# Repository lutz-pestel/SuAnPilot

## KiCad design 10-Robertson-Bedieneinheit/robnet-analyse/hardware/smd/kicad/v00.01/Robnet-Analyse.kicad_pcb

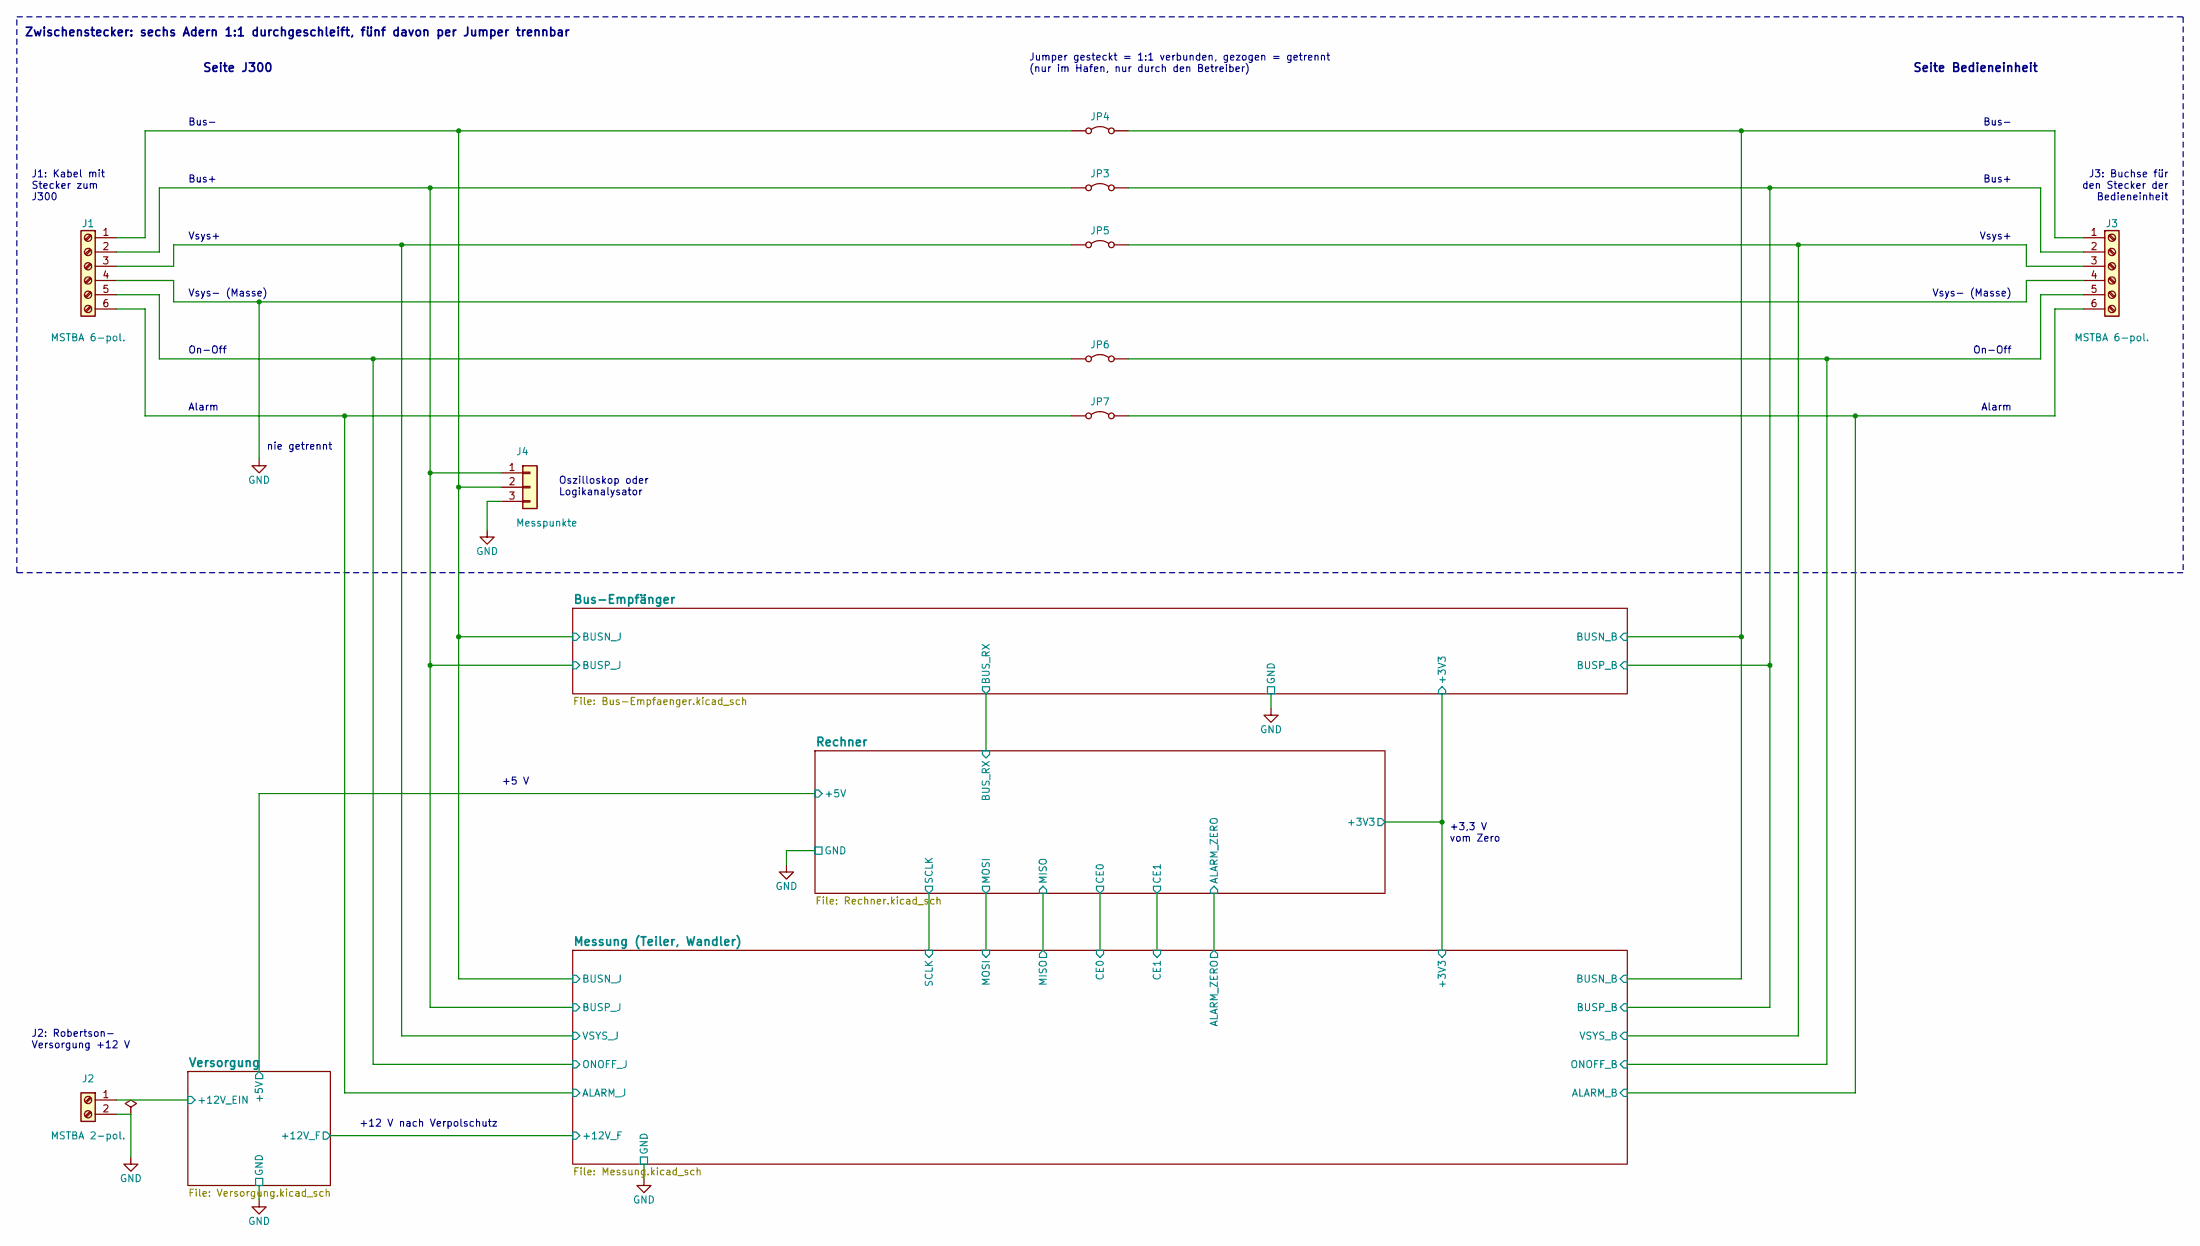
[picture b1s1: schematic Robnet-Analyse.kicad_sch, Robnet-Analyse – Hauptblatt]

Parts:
J1, J3: MSTBA 6-pol.; PhoenixContact_MSTBA_2,5_6-G-5,08_1x06_P5.08mm_Horizontal
J2: MSTBA 2-pol.; PhoenixContact_MSTBA_2,5_2-G-5,08_1x02_P5.08mm_Horizontal
J4: Messpunkte; PinHeader_1x03_P2.54mm_Vertical
JP3, JP4, JP5, JP6, JP7: Jumper; PinHeader_1x02_P2.54mm_Vertical

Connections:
/Bus-Empfänger/BUSN_B: J3.1, JP4.2 (B); also elsewhere on the board
/Bus-Empfänger/BUSN_J: J1.1, J4.2, JP4.1 (A); also elsewhere on the board
/Bus-Empfänger/BUSP_B: J3.2, JP3.2 (B); also elsewhere on the board
/Bus-Empfänger/BUSP_J: J1.2, J4.1, JP3.1 (A); also elsewhere on the board
/Messung (Teiler, Wandler)/ALARM_B: J3.6, JP7.2 (B); also elsewhere on the board
/Messung (Teiler, Wandler)/ALARM_J: J1.6, JP7.1 (A); also elsewhere on the board
/Messung (Teiler, Wandler)/ONOFF_B: J3.5, JP6.2 (B); also elsewhere on the board
/Messung (Teiler, Wandler)/ONOFF_J: J1.5, JP6.1 (A); also elsewhere on the board
/Messung (Teiler, Wandler)/VSYS_B: J3.3, JP5.2 (B); also elsewhere on the board
/Messung (Teiler, Wandler)/VSYS_J: J1.3, JP5.1 (A); also elsewhere on the board
/Versorgung/+12V_EIN: J2.1; also elsewhere on the board
GND: J1.4, J2.2, J3.4, J4.3; also elsewhere on the board

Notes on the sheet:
Zwischenstecker: sechs Adern 1:1 durchgeschleift, fünf davon per Jumper trennbar
Seite J300
Seite Bedieneinheit
Jumper gesteckt = 1:1 verbunden, gezogen = getrennt (nur im Hafen, nur durch den Betreiber)
J1: Kabel mit Stecker zum J300
J3: Buchse für den Stecker der Bedieneinheit
Bus−
Bus+
Vsys+
Vsys− (Masse)
On-Off
Alarm
nie getrennt
Oszilloskop oder Logikanalysator
J2: Robertson- Versorgung +12 V
+12 V nach Verpolschutz
+5 V
+3,3 V vom Zero

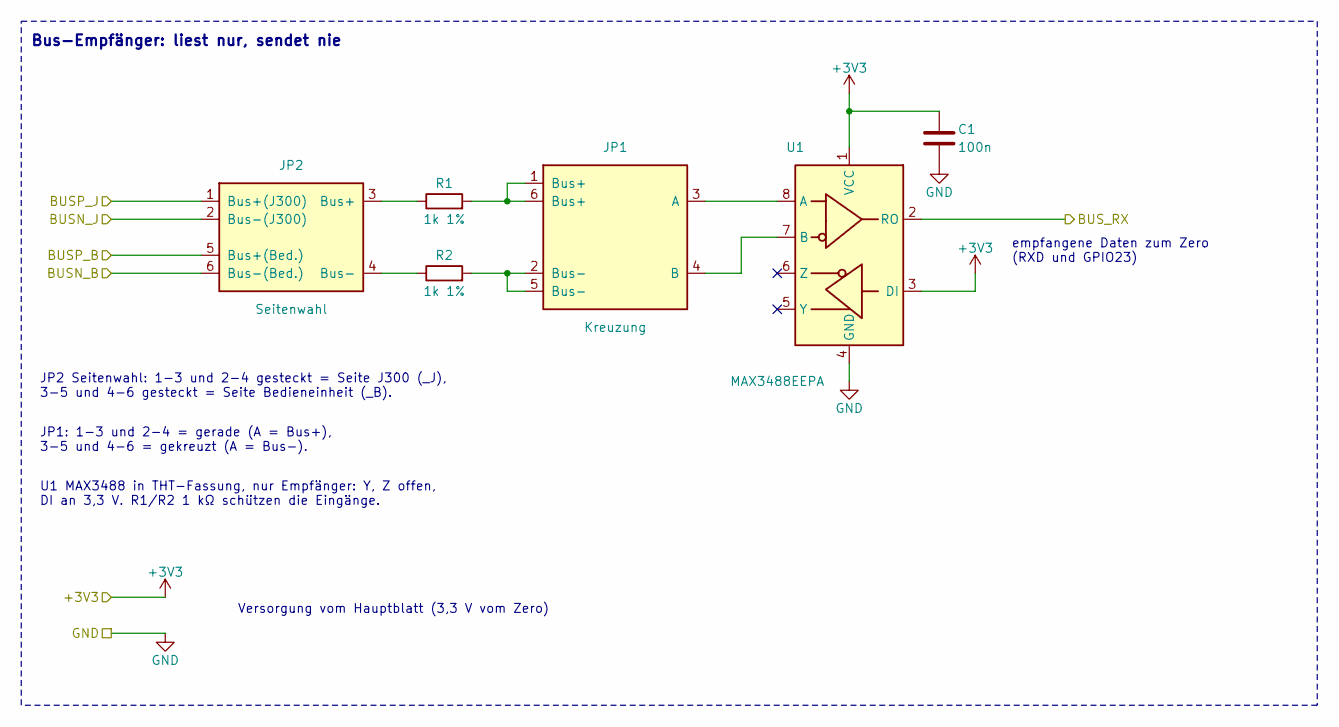
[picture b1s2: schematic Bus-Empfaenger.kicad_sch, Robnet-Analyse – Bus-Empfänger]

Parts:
C1: 100n; C_1206_3216Metric; LCSC Part # C24497
JP1: Kreuzung; PinHeader_2x03_P2.54mm_Vertical
JP2: Seitenwahl; PinHeader_2x03_P2.54mm_Vertical
R1, R2: 1k 1%; R_0805_2012Metric; LCSC Part # C17513
U1: MAX3488EEPA; DIP-8_W7.62mm_Socket

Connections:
/Bus-Empfänger/+3V3: C1.1, U1.1 (VCC), U1.3 (DI); also elsewhere on the board
/Bus-Empfänger/BUSN_B: JP2.6 (Bus−(Bed.)); also elsewhere on the board
/Bus-Empfänger/BUSN_J: JP2.2 (Bus−(J300)); also elsewhere on the board
/Bus-Empfänger/BUSP_B: JP2.5 (Bus+(Bed.)); also elsewhere on the board
/Bus-Empfänger/BUSP_J: JP2.1 (Bus+(J300)); also elsewhere on the board
/Bus-Empfänger/BUS_RX: U1.2 (RO); also elsewhere on the board
GND: C1.2, U1.4 (GND); also elsewhere on the board
unnamed: JP1.3 (A), U1.8 (A)
unnamed: JP1.4 (B), U1.7 (B)
unnamed: JP1.1 (Bus+), JP1.6 (Bus+), R1.2
unnamed: JP1.2 (Bus−), JP1.5 (Bus−), R2.2
unnamed: JP2.3 (Bus+), R1.1
unnamed: JP2.4 (Bus−), R2.1

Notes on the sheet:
Bus-Empfänger: liest nur, sendet nie
Versorgung vom Hauptblatt (3,3 V vom Zero)
JP2 Seitenwahl: 1-3 und 2-4 gesteckt = Seite J300 (_J), 3-5 und 4-6 gesteckt = Seite Bedieneinheit (_B).
JP1: 1-3 und 2-4 = gerade (A = Bus+), 3-5 und 4-6 = gekreuzt (A = Bus−).
U1 MAX3488 in THT-Fassung, nur Empfänger: Y, Z offen, DI an 3,3 V. R1/R2 1 kΩ schützen die Eingänge.
empfangene Daten zum Zero (RXD und GPIO23)

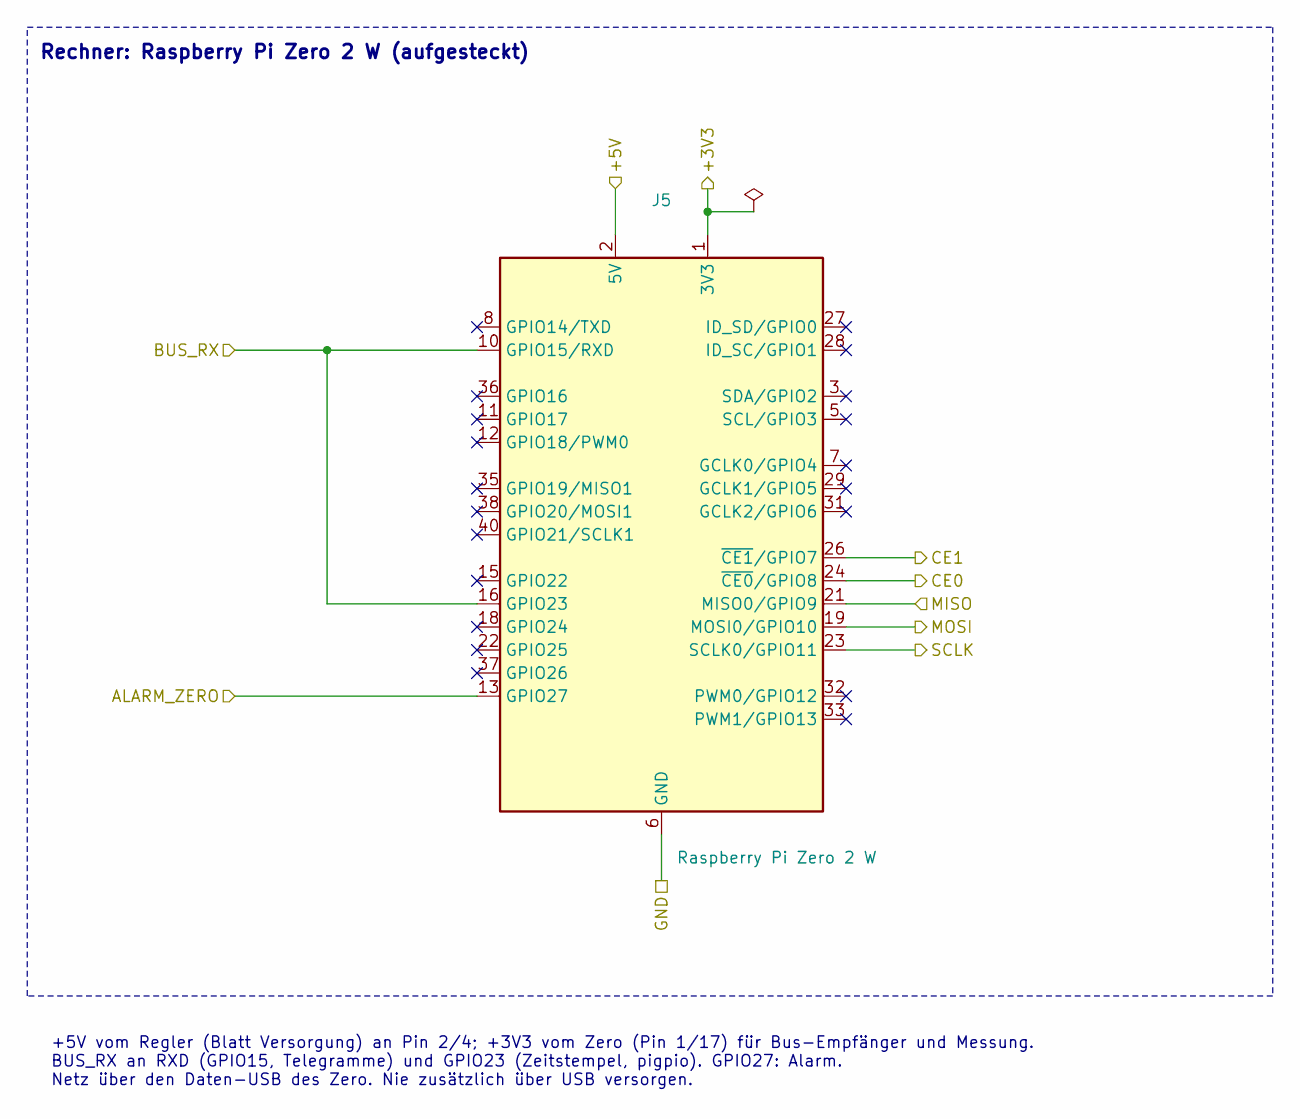
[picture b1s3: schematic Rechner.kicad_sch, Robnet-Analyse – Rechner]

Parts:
J5: Raspberry Pi Zero 2 W; Raspberry_Pi_Zero_kopfueber

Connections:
/Bus-Empfänger/+3V3: J5.1 (3V3), J5.17 (3V3); also elsewhere on the board
/Bus-Empfänger/BUS_RX: J5.10 (GPIO15/RXD), J5.16 (GPIO23); also elsewhere on the board
/Messung (Teiler, Wandler)/ALARM_ZERO: J5.13 (GPIO27); also elsewhere on the board
/Messung (Teiler, Wandler)/CE0: J5.24 (~CE0/GPIO8); also elsewhere on the board
/Messung (Teiler, Wandler)/CE1: J5.26 (~CE1/GPIO7); also elsewhere on the board
/Messung (Teiler, Wandler)/MISO: J5.21 (MISO0/GPIO9); also elsewhere on the board
/Messung (Teiler, Wandler)/MOSI: J5.19 (MOSI0/GPIO10); also elsewhere on the board
/Messung (Teiler, Wandler)/SCLK: J5.23 (SCLK0/GPIO11); also elsewhere on the board
/Rechner/+5V: J5.2 (5V), J5.4 (5V); also elsewhere on the board
GND: J5.6 (GND), J5.9 (GND), J5.14 (GND), J5.20 (GND), J5.25 (GND), J5.30 (GND), J5.34 (GND), J5.39 (GND); also elsewhere on the board

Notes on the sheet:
Rechner: Raspberry Pi Zero 2 W (aufgesteckt)
+5V vom Regler (Blatt Versorgung) an Pin 2/4; +3V3 vom Zero (Pin 1/17) für Bus-Empfänger und Messung. BUS_RX an RXD (GPIO15, Telegramme) und GPIO23 (Zeitstempel, pigpio). GPIO27: Alarm. Netz über den Daten-USB des Zero. Nie zusätzlich über USB versorgen.

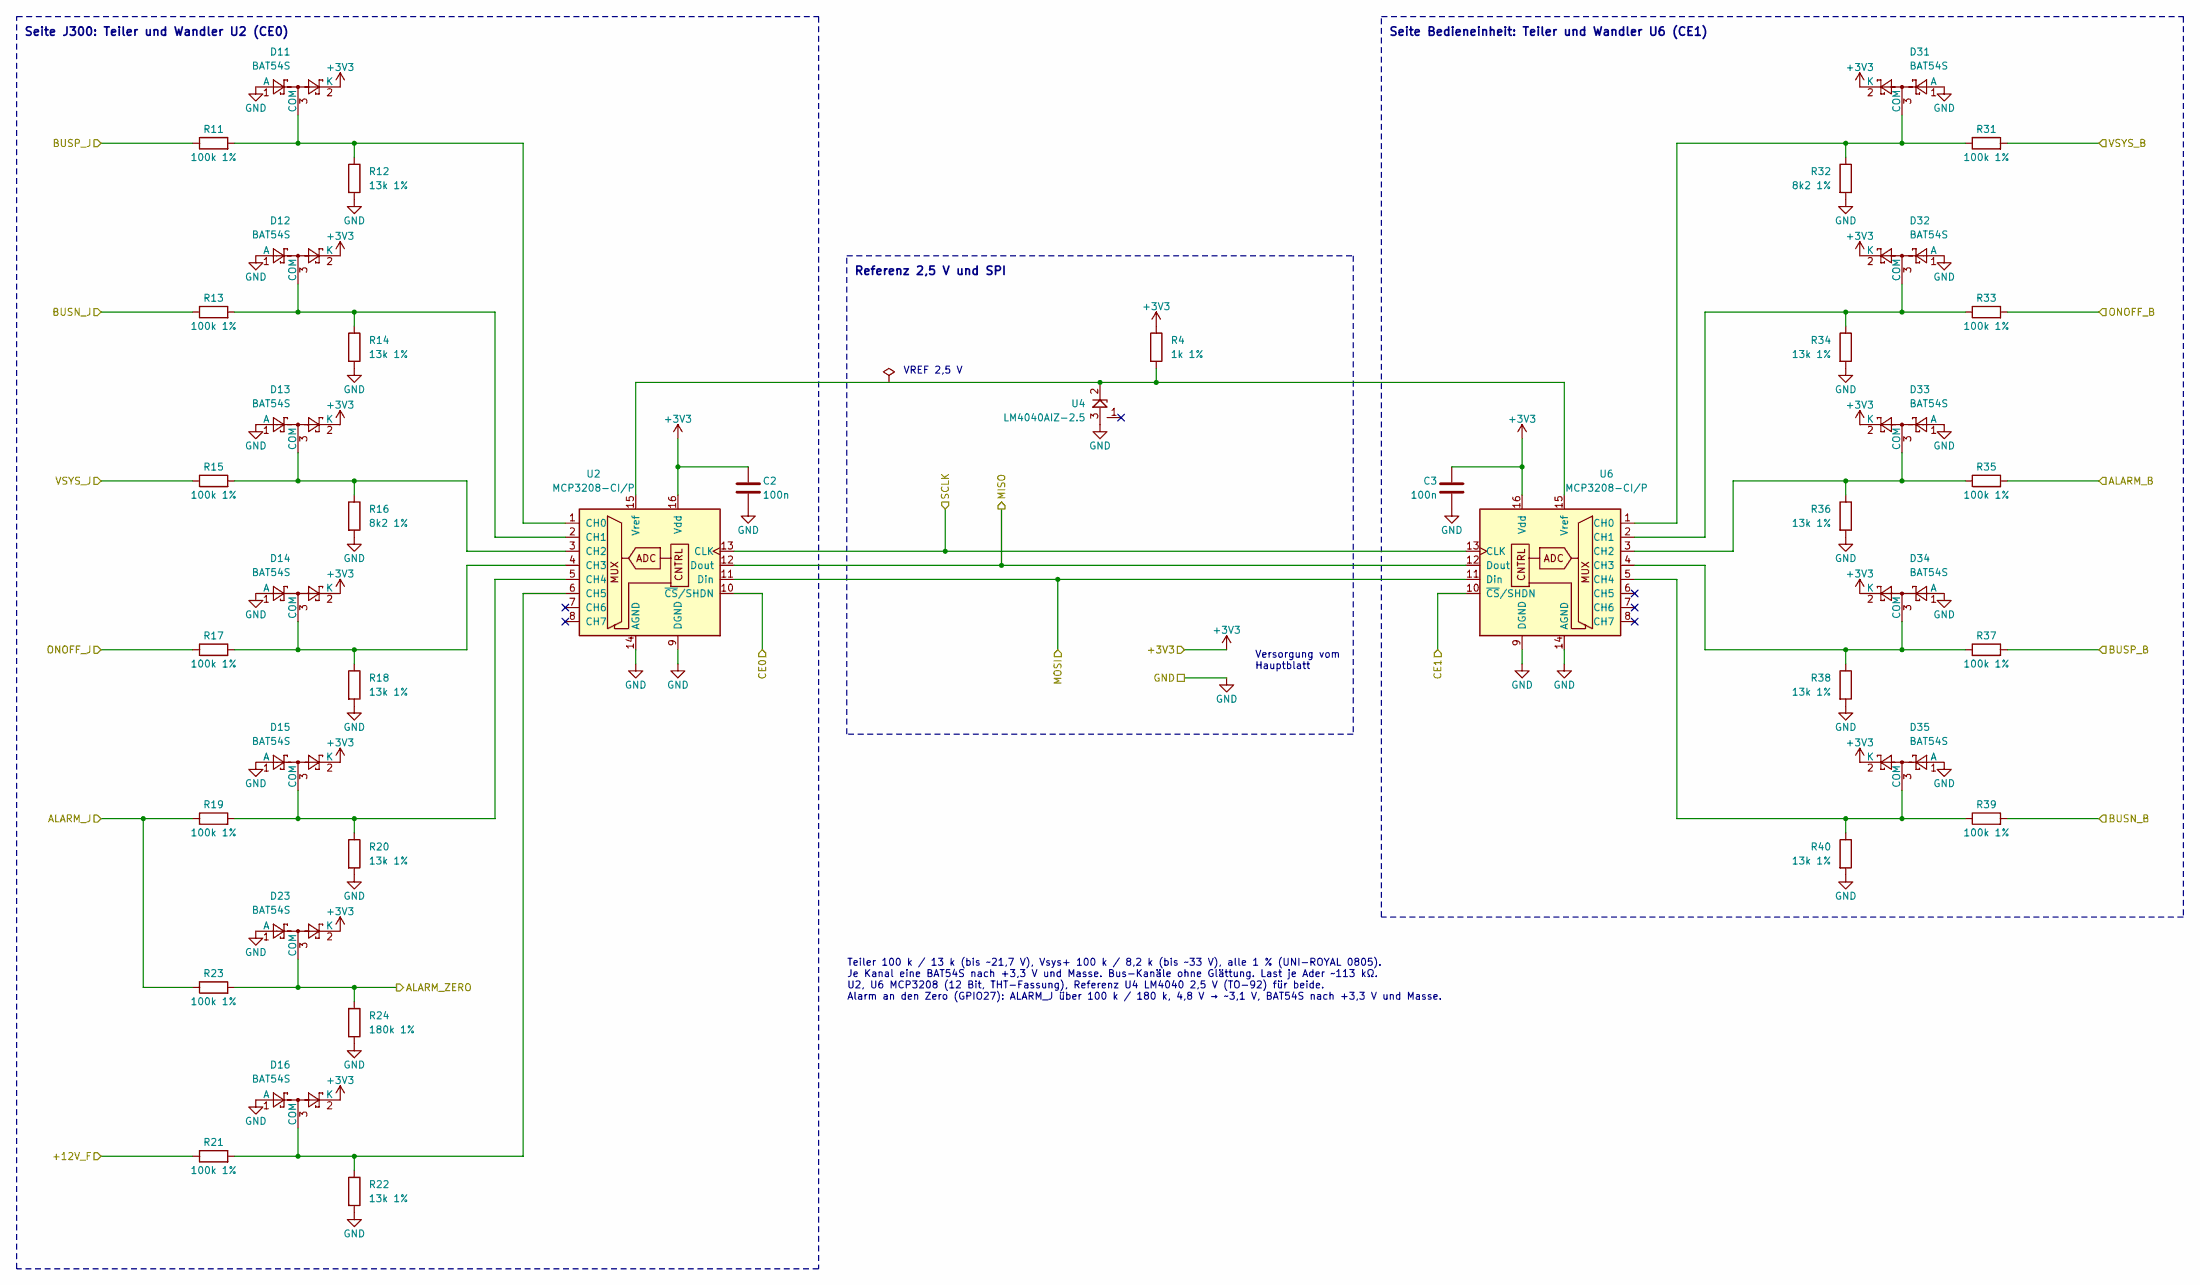
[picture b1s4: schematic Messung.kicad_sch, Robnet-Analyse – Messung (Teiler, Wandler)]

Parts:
C2, C3: 100n; C_1206_3216Metric; LCSC Part # C24497
D11, D12, D13, D14, D15, D16, D23, D31, D32, D33, D34, D35: BAT54S; SOT-23; LCSC Part # C7420333
R4: 1k 1%; R_0805_2012Metric; LCSC Part # C17513
R11, R13, R15, R17, R19, R21, R23, R31, R33, R35, R37, R39: 100k 1%; R_0805_2012Metric; LCSC Part # C149504
R12, R14, R18, R20, R22, R34, R36, R38, R40: 13k 1%; R_0805_2012Metric; LCSC Part # C17455
R16, R32: 8k2 1%; R_0805_2012Metric; LCSC Part # C17828
R24: 180k 1%; R_0805_2012Metric; LCSC Part # C17501
U2, U6: MCP3208-CI/P; DIP-16_W7.62mm_Socket
U4: LM4040AIZ-2.5; TO-92_Inline

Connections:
/Bus-Empfänger/+3V3: C2.1, C3.1, D11.2 (K), D12.2 (K), D13.2 (K), D14.2 (K), D15.2 (K), D16.2 (K), D23.2 (K), D31.2 (K), D32.2 (K), D33.2 (K), D34.2 (K), D35.2 (K), R4.1, U2.16 (Vdd), U6.16 (Vdd); also elsewhere on the board
/Bus-Empfänger/BUSN_B: R39.2; also elsewhere on the board
/Bus-Empfänger/BUSN_J: R13.1; also elsewhere on the board
/Bus-Empfänger/BUSP_B: R37.2; also elsewhere on the board
/Bus-Empfänger/BUSP_J: R11.1; also elsewhere on the board
/Messung (Teiler, Wandler)/+12V_F: R21.1; also elsewhere on the board
/Messung (Teiler, Wandler)/ALARM_B: R35.2; also elsewhere on the board
/Messung (Teiler, Wandler)/ALARM_J: R19.1, R23.1; also elsewhere on the board
/Messung (Teiler, Wandler)/ALARM_ZERO: D23.3 (COM), R23.2, R24.1; also elsewhere on the board
/Messung (Teiler, Wandler)/CE0: U2.10 (~CS/SHDN); also elsewhere on the board
/Messung (Teiler, Wandler)/CE1: U6.10 (~CS/SHDN); also elsewhere on the board
/Messung (Teiler, Wandler)/MISO: U2.12 (Dout), U6.12 (Dout); also elsewhere on the board
/Messung (Teiler, Wandler)/MOSI: U2.11 (Din), U6.11 (Din); also elsewhere on the board
/Messung (Teiler, Wandler)/ONOFF_B: R33.2; also elsewhere on the board
/Messung (Teiler, Wandler)/ONOFF_J: R17.1; also elsewhere on the board
/Messung (Teiler, Wandler)/SCLK: U2.13 (CLK), U6.13 (CLK); also elsewhere on the board
/Messung (Teiler, Wandler)/VSYS_B: R31.2; also elsewhere on the board
/Messung (Teiler, Wandler)/VSYS_J: R15.1; also elsewhere on the board
GND: C2.2, C3.2, D11.1 (A), D12.1 (A), D13.1 (A), D14.1 (A), D15.1 (A), D16.1 (A), D23.1 (A), D31.1 (A), D32.1 (A), D33.1 (A), D34.1 (A), D35.1 (A), R12.2, R14.2, R16.2, R18.2, R20.2, R22.2, R24.2, R32.2, R34.2, R36.2, R38.2, R40.2, U2.9 (DGND), U2.14 (AGND), U4.3 (A), U6.9 (DGND), U6.14 (AGND); also elsewhere on the board
unnamed: D11.3 (COM), R11.2, R12.1, U2.1 (CH0)
unnamed: D12.3 (COM), R13.2, R14.1, U2.2 (CH1)
unnamed: D13.3 (COM), R15.2, R16.1, U2.3 (CH2)
unnamed: D14.3 (COM), R17.2, R18.1, U2.4 (CH3)
unnamed: D15.3 (COM), R19.2, R20.1, U2.5 (CH4)
unnamed: D16.3 (COM), R21.2, R22.1, U2.6 (CH5)
unnamed: D31.3 (COM), R31.1, R32.1, U6.1 (CH0)
unnamed: D32.3 (COM), R33.1, R34.1, U6.2 (CH1)
unnamed: D33.3 (COM), R35.1, R36.1, U6.3 (CH2)
unnamed: D34.3 (COM), R37.1, R38.1, U6.4 (CH3)
unnamed: D35.3 (COM), R39.1, R40.1, U6.5 (CH4)
unnamed: R4.2, U2.15 (Vref), U4.2 (K), U6.15 (Vref)

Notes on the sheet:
Seite J300: Teiler und Wandler U2 (CE0)
Seite Bedieneinheit: Teiler und Wandler U6 (CE1)
Referenz 2,5 V und SPI
VREF 2,5 V
Versorgung vom Hauptblatt
Teiler 100 k / 13 k (bis ~21,7 V), Vsys+ 100 k / 8,2 k (bis ~33 V), alle 1 % (UNI-ROYAL 0805). Je Kanal eine BAT54S nach +3,3 V und Masse. Bus-Kanäle ohne Glättung. Last je Ader ~113 kΩ. U2, U6 MCP3208 (12 Bit, THT-Fassung), Referenz U4 LM4040 2,5 V (TO-92) für beide. Alarm an den Zero (GPIO27): AL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

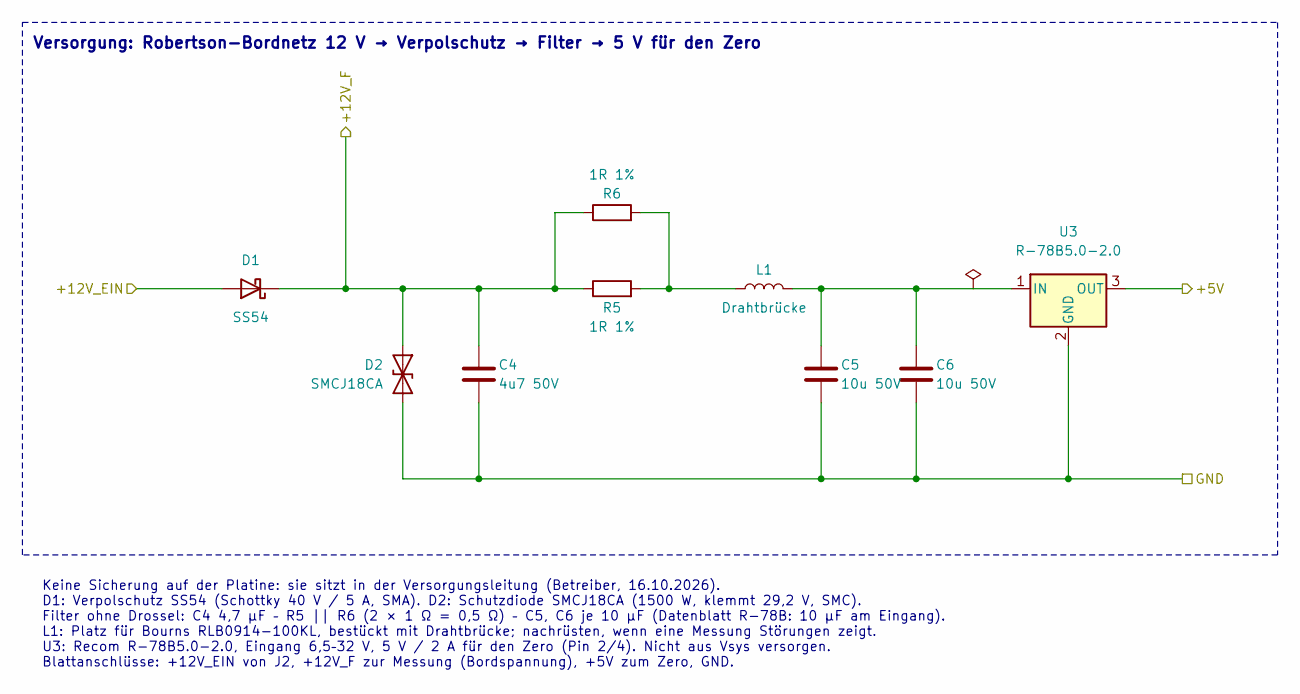
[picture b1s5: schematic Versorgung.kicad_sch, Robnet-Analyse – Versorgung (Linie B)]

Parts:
C4: 4u7 50V; C_1206_3216Metric; LCSC Part # C29823
C5, C6: 10u 50V; C_1206_3216Metric; LCSC Part # C13585
D1: SS54; D_SMA; LCSC Part # C22452
D2: SMCJ18CA; D_SMC; LCSC Part # C41411753
L1: Drahtbrücke; L_Radial_D10.0mm_P5.00mm_Fastron_07P
R5, R6: 1R 1%; R_1206_3216Metric; LCSC Part # C17928
U3: R-78B5.0-2.0; Converter_DCDC_RECOM_R-78B-2.0_THT

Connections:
/Messung (Teiler, Wandler)/+12V_F: C4.1, D1.1 (K), D2.1 (A1), R5.1, R6.1; also elsewhere on the board
/Rechner/+5V: U3.3 (OUT); also elsewhere on the board
/Versorgung/+12V_EIN: D1.2 (A); also elsewhere on the board
GND: C4.2, C5.2, C6.2, D2.2 (A2), U3.2 (GND); also elsewhere on the board
unnamed: L1.1, R5.2, R6.2
unnamed: C5.1, C6.1, L1.2, U3.1 (IN)

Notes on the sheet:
Versorgung: Robertson-Bordnetz 12 V → Verpolschutz → Filter → 5 V für den Zero
Keine Sicherung auf der Platine: sie sitzt in der Versorgungsleitung (Betreiber, 16.10.2026). D1: Verpolschutz SS54 (Schottky 40 V / 5 A, SMA). D2: Schutzdiode SMCJ18CA (1500 W, klemmt 29,2 V, SMC). Filter ohne Drossel: C4 4,7 µF – R5 || R6 (2 × 1 Ω = 0,5 Ω) – C5, C6 je 10 µF (Datenblatt R-78B: 10 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

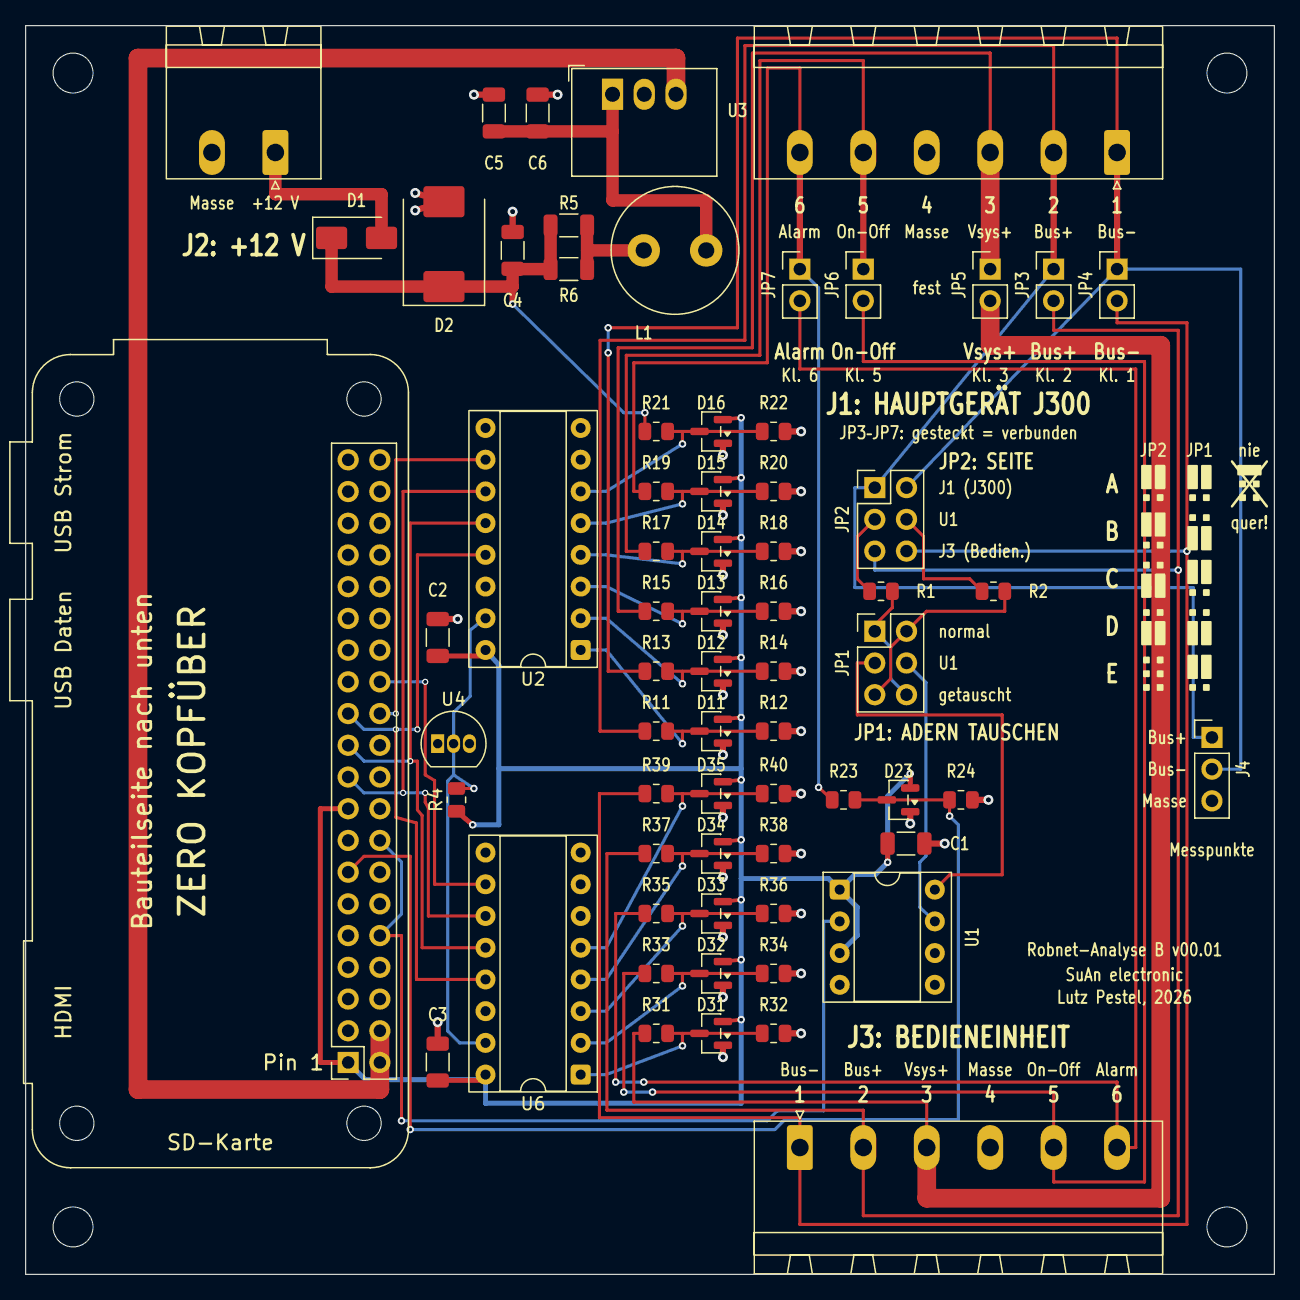
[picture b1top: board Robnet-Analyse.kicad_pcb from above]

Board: 2 copper layers, 100.0 x 100.0 mm, 71 parts (0 on the bottom side), 42 nets.

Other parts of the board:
H1, H2, H3, H4: M3; MountingHole_3.2mm_M3

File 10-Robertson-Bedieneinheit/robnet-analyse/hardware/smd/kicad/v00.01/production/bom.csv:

Designator,Footprint,Quantity,Value,LCSC Part #
"C1, C2, C3",1206,3,100n,C24497
C4,1206,1,4u7 50V,C29823
"C5, C6",1206,2,10u 50V,C13585
D1,D_SMA,1,SS54,C22452
"D11, D12, D13, D14, D15, D16, D23, D31, D32, D33, D34, D35",SOT-23,12,BAT54S,C7420333
D2,D_SMC,1,SMCJ18CA,C41411753
"R1, R2, R4",0805,3,1k 1%,C17513
"R11, R13, R15, R17, R19, R21, R23, R31, R33, R35, R37, R39",0805,12,100k 1%,C149504
"R12, R14, R18, R20, R22, R34, R36, R38, R40",0805,9,13k 1%,C17455
"R16, R32",0805,2,8k2 1%,C17828
R24,0805,1,180k 1%,C17501
"R5, R6",1206,2,1R 1%,C17928

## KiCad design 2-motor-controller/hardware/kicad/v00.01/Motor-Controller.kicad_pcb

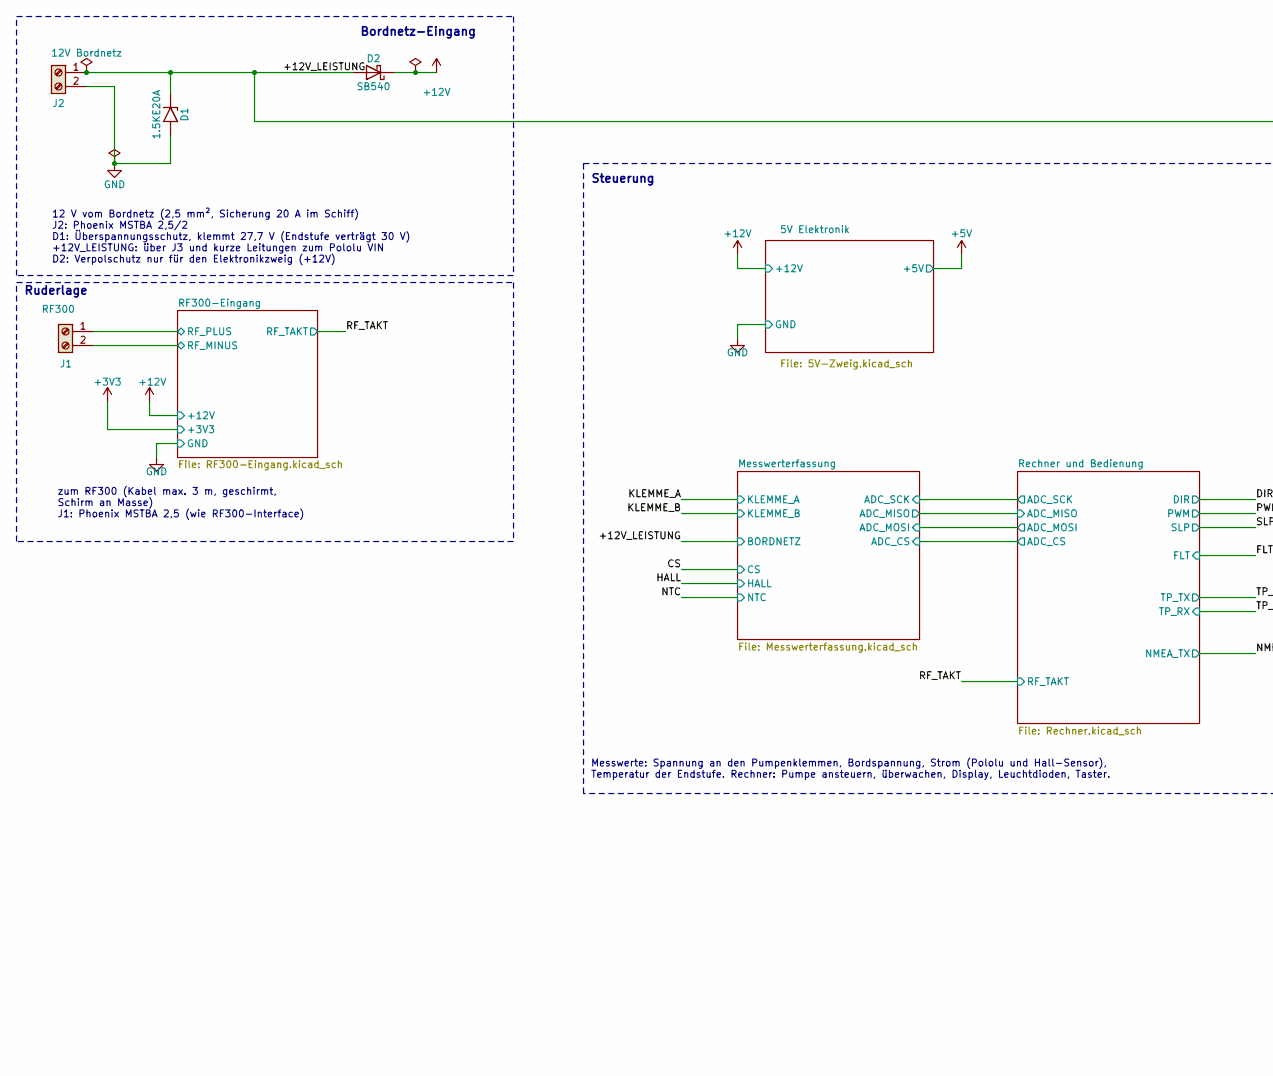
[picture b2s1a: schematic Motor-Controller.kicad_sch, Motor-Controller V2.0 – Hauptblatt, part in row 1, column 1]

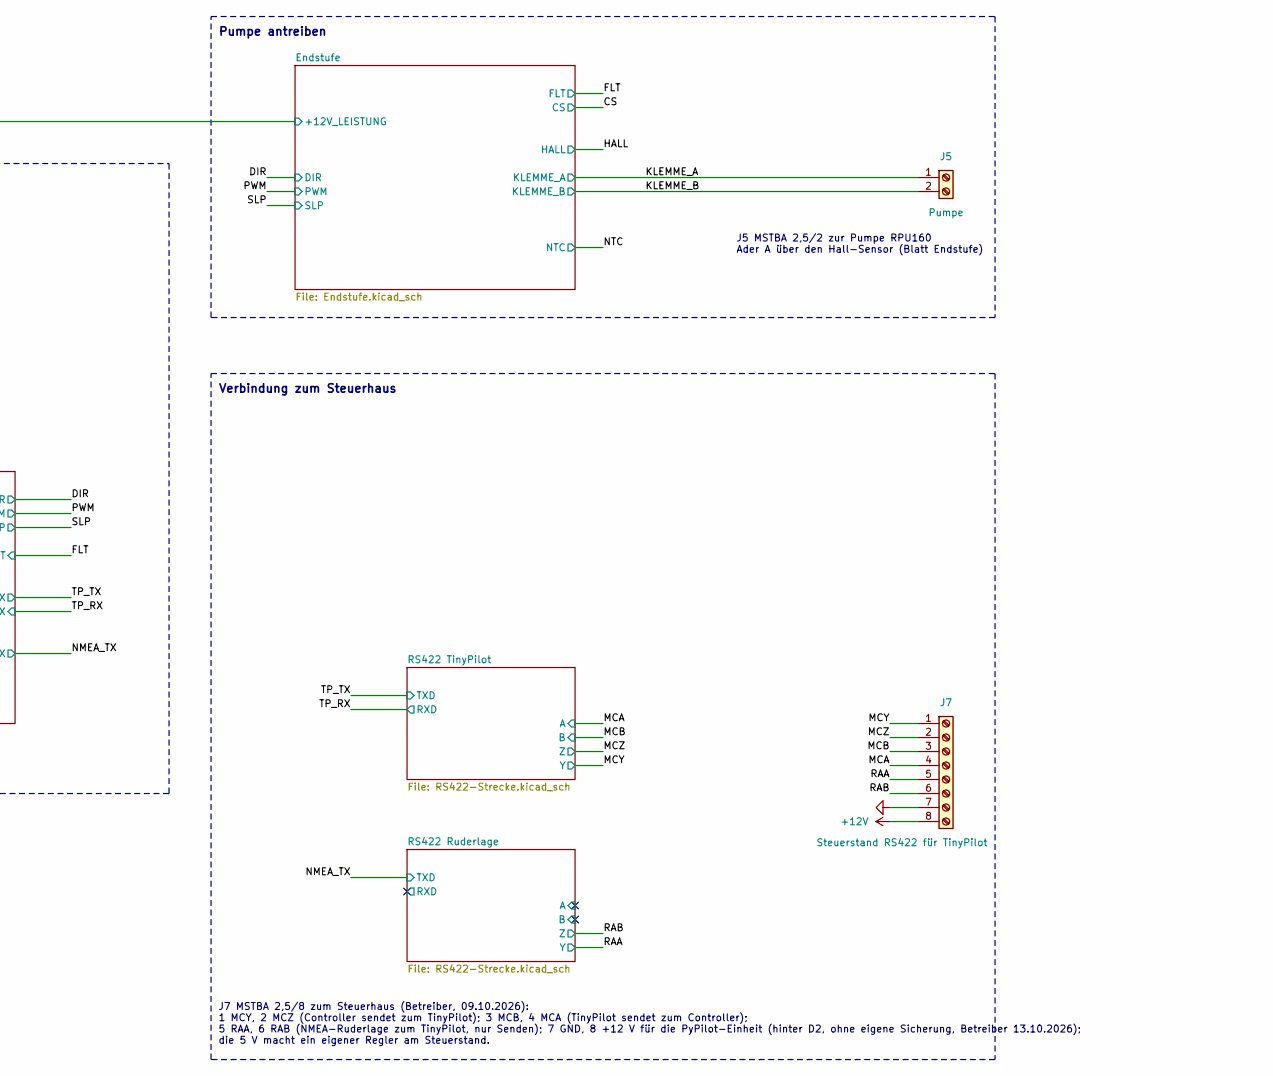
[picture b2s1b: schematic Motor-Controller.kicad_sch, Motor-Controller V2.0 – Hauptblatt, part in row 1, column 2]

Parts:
D1: 1.5KE20A; D_DO-201AE_P15.24mm_Horizontal
D2: SB540; D_DO-201AD_P15.24mm_Horizontal
J1: RF300; PhoenixContact_MSTBA_2,5_2-G-5,08_1x02_P5.08mm_Horizontal
J2: 12V Bordnetz; Degson_DG301-5.0-02P
J5: Pumpe; PhoenixContact_MSTBA_2,5_2-G-5,08_1x02_P5.08mm_Horizontal
J7: Steuerstand RS422 für TinyPilot; PhoenixContact_MSTBA_2,5_8-G-5,08_1x08_P5.08mm_Horizontal

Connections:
+12V: D2.1 (K), J7.8; also elsewhere on the board
/+12V_LEISTUNG: D1.1 (A1), D2.2 (A), J2.1; also elsewhere on the board
/KLEMME_A: J5.1; also elsewhere on the board
/KLEMME_B: J5.2; also elsewhere on the board
/MCA: J7.4; also elsewhere on the board
/MCB: J7.3; also elsewhere on the board
/MCY: J7.1; also elsewhere on the board
/MCZ: J7.2; also elsewhere on the board
/RAA: J7.5; also elsewhere on the board
/RAB: J7.6; also elsewhere on the board
/RF300-Eingang/RF_PLUS: J1.1; also elsewhere on the board
GND: D1.2 (A2), J1.2, J2.2, J7.7; also elsewhere on the board

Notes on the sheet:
Verbindung zum Steuerhaus
J7 MSTBA 2,5/8 zum Steuerhaus (Betreiber, 09.10.2026): 1 MCY, 2 MCZ (Controller sendet zum TinyPilot); 3 MCB, 4 MCA (TinyPilot sendet zum Controller); 5 RAA, 6 RAB (NMEA-Ruderlage zum TinyPilot, nur Senden); 7 GND, 8 +12 V für die PyPilot-Einheit (hinter D2, ohne eigene Sicherung, Betreiber 13.10.2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
Steuerung
Bordnetz-Eingang
Pumpe antreiben
Messwerte: Spannung an den Pumpenklemmen, Bordspannung, Strom (Pololu und Hall-Sensor), Temperatur der Endstufe. Rechner: Pumpe ansteuern, überwachen, Display, Leuchtdioden, Taster.
Ruderlage
zum RF300 (Kabel max. 3 m, geschirmt, Schirm an Masse) J1: Phoenix MSTBA 2,5 (wie RF300-Interface)
12 V vom Bordnetz (2,5 mm², Sicherung 20 A im Schiff) J2: Phoenix MSTBA 2,5/2 D1: Überspannungsschutz, klemmt 27,7 V (Endstufe verträgt 30 V) +12V_LEISTUNG: über J3 und kurze Leitungen zum Pololu VIN D2: Verpolschutz nur für den Elektronikzweig (+12V)
J5 MSTBA 2,5/2 zur Pumpe RPU160 Ader A über den Hall-Sensor (Blatt Endstufe)

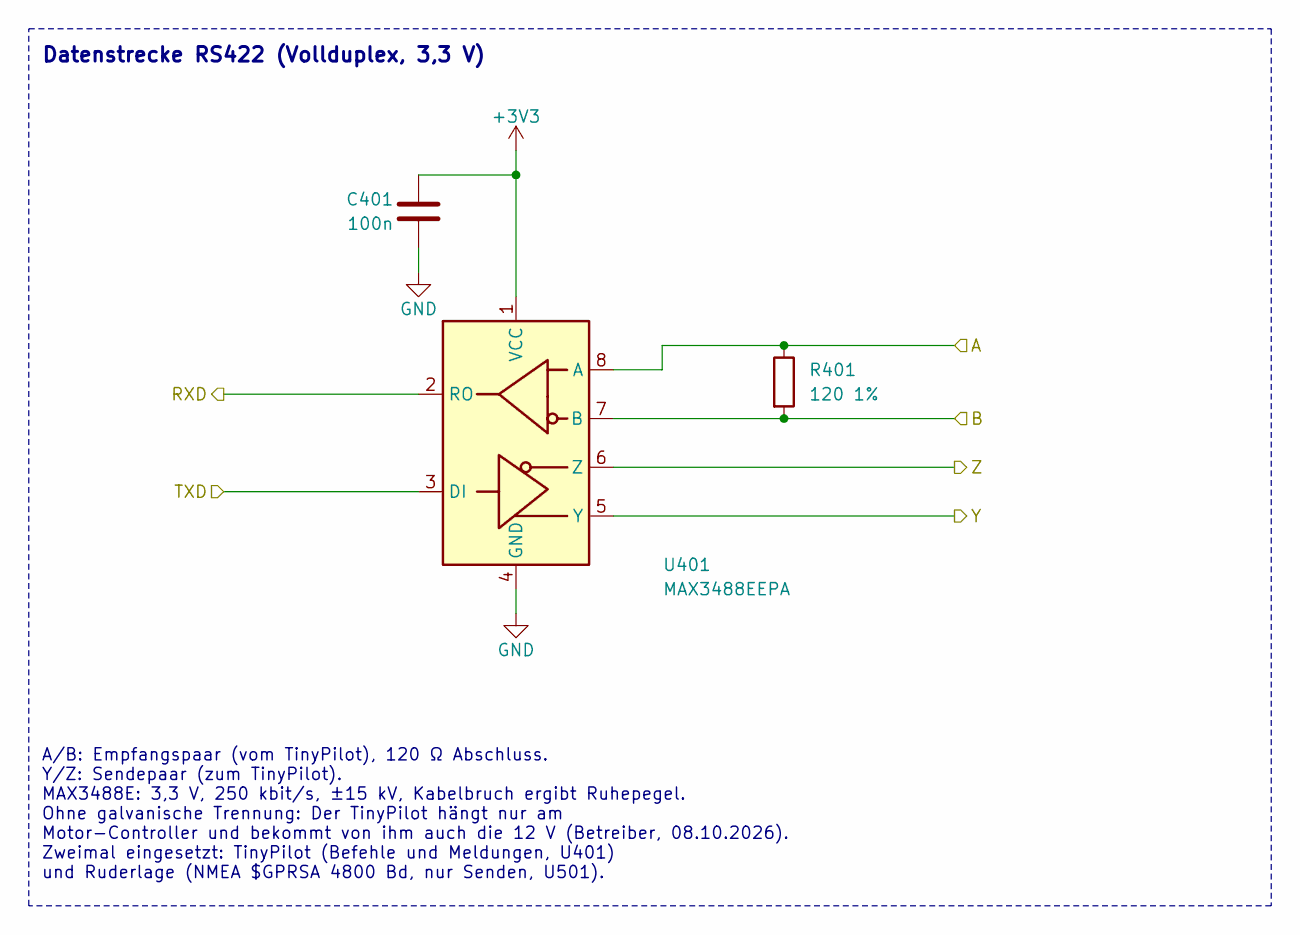
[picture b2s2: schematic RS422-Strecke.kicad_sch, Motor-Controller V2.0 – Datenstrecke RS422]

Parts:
C401: 100n; C_KEMET_C320_L5.1mm_W4.1mm_P2.54mm
R401: 120 1%; R_Axial_DIN0207_L6.3mm_D2.5mm_P10.16mm_Horizontal
U401: MAX3488EEPA; DIP-8_W7.62mm

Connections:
+3V3: C401.1, U401.1 (VCC); also elsewhere on the board
/MCA: R401.1, U401.8 (A); also elsewhere on the board
/MCB: R401.2, U401.7 (B); also elsewhere on the board
/MCY: U401.5 (Y); also elsewhere on the board
/MCZ: U401.6 (Z); also elsewhere on the board
/TP_RX: U401.2 (RO); also elsewhere on the board
/TP_TX: U401.3 (DI); also elsewhere on the board
GND: C401.2, U401.4 (GND); also elsewhere on the board

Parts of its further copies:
C501: 100n; C_KEMET_C320_L5.1mm_W4.1mm_P2.54mm
R501: 120 1%; R_Axial_DIN0207_L6.3mm_D2.5mm_P10.16mm_Horizontal
U501: MAX3488EEPA; DIP-8_W7.62mm

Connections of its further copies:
+3V3: C501.1, U501.1 (VCC); also elsewhere on the board
/NMEA_TX: U501.3 (DI); also elsewhere on the board
/RAA: U501.5 (Y); also elsewhere on the board
/RAB: U501.6 (Z); also elsewhere on the board
/RS422 Ruderlage/A: R501.1, U501.8 (A)
/RS422 Ruderlage/B: R501.2, U501.7 (B)
/RS422 Ruderlage/RXD: U501.2 (RO)
GND: C501.2, U501.4 (GND); also elsewhere on the board

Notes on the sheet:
Datenstrecke RS422 (Vollduplex, 3,3 V)
A/B: Empfangspaar (vom TinyPilot), 120 Ω Abschluss. Y/Z: Sendepaar (zum TinyPilot). MAX3488E: 3,3 V, 250 kbit/s, ±15 kV, Kabelbruch ergibt Ruhepegel. Ohne galvanische Trennung: Der TinyPilot hängt nur am Motor-Controller und bekommt von ihm auch die 12 V (Betreiber, 08.10.2026). Zweimal eingesetzt: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
